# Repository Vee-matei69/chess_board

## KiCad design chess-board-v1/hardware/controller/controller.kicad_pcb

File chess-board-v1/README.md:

Electronic chess board

# get the initial board layout - which squares the pieces are on - 
when initializing, each piece is given a xpos and ypos

# if a piece is lifted, scan the board -
-get the new layout of the board - empty squares and occupied squares[current_matrix] - get the row-col (lifted_square)
-go through each board piece and find the one that has xpos and ypos same as the (lifted_square)
-check for possible moves - (check for possible squares) - feed them into an array
-compare the [possible_squares] and [current_matrix] - 
-if 

possible_squares, available_squares, valid_squares

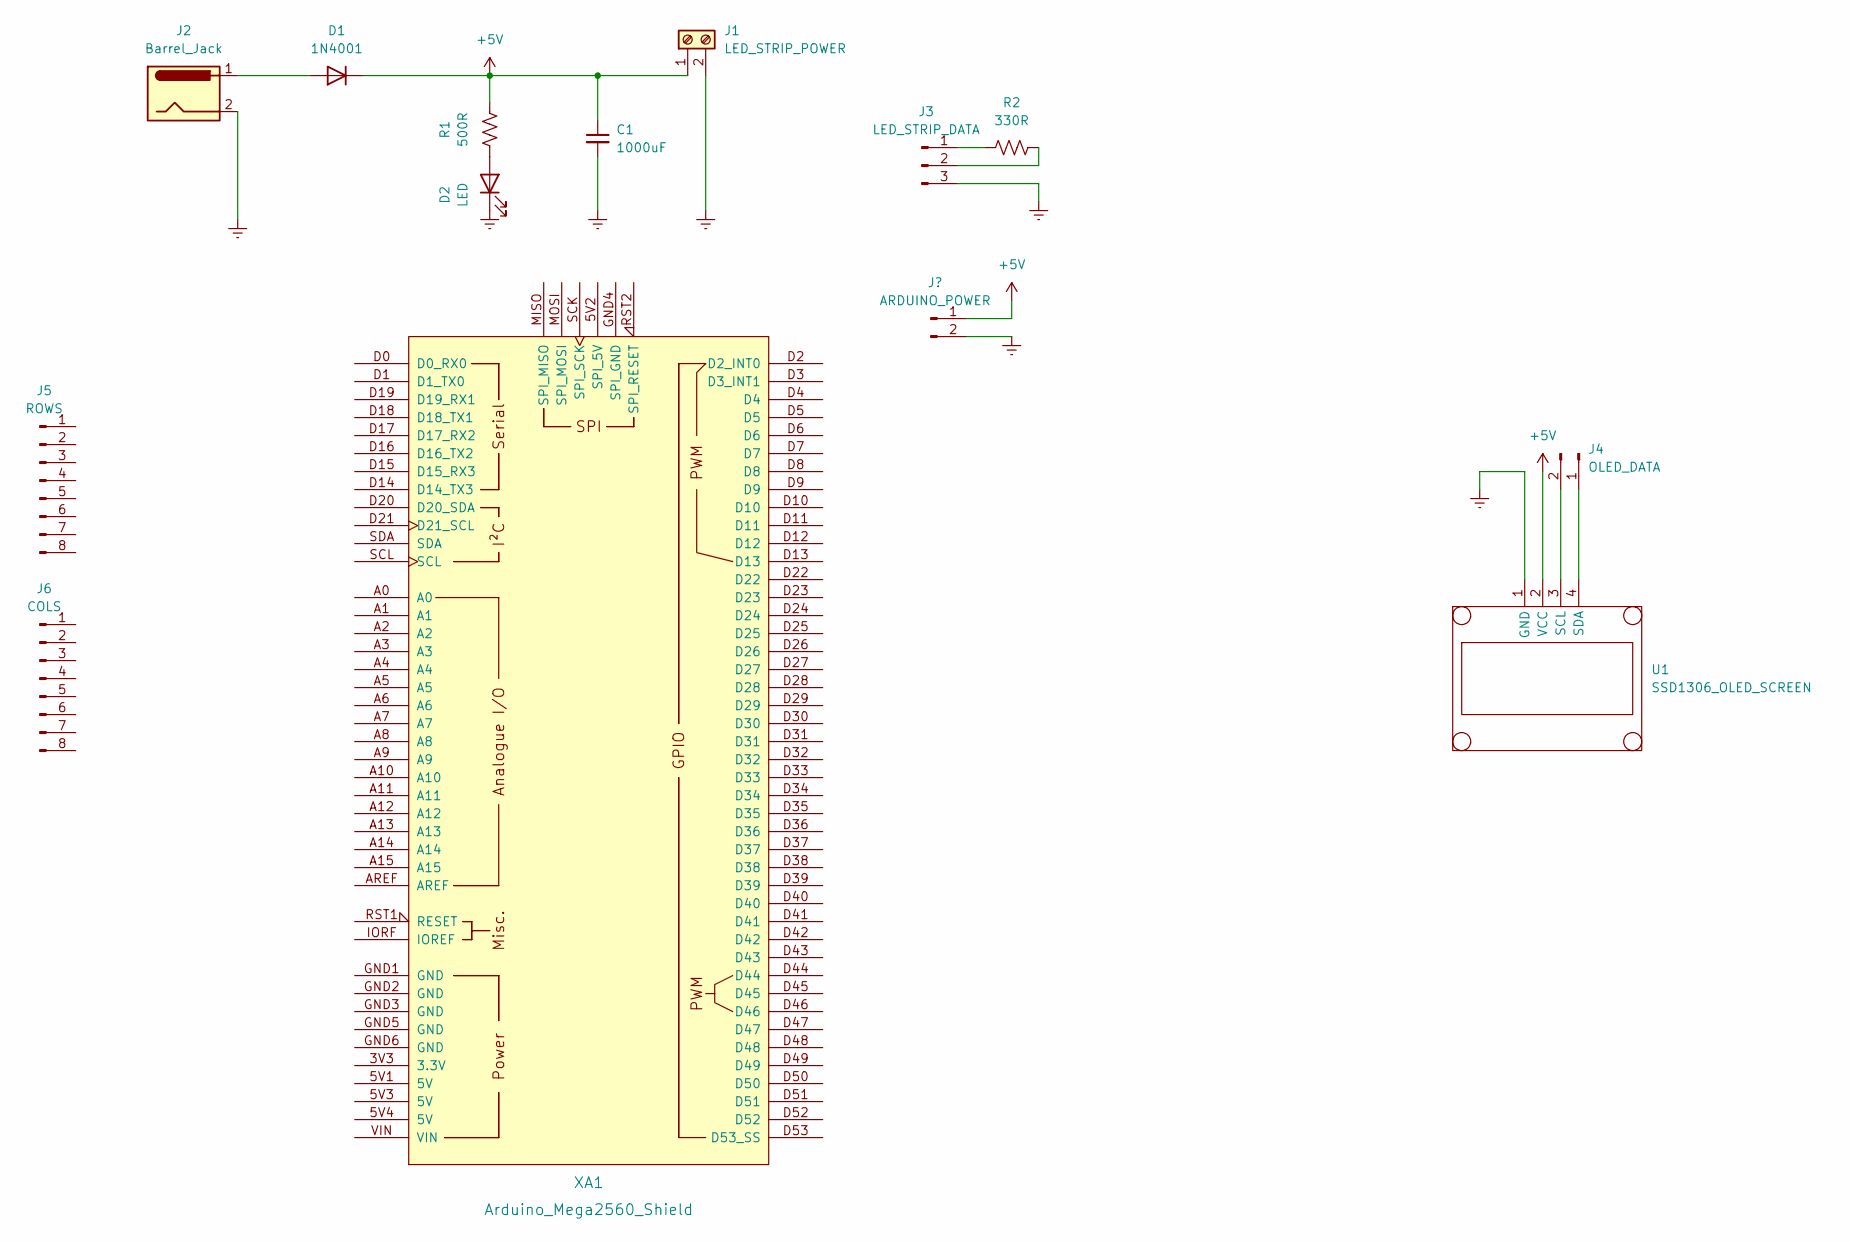
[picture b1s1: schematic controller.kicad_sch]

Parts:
C1: 1000uF; CP_Radial_D8.0mm_P3.50mm
D1: 1N4001; D_DO-41_SOD81_P10.16mm_Horizontal
D2: LED; LED_D4.0mm
J1: LED_STRIP_POWER; TerminalBlock_bornier-2_P5.08mm
J2: Barrel_Jack; BarrelJack_Wuerth_6941xx301002
J3: LED_STRIP_DATA; PinHeader_1x03_P2.54mm_Vertical
J4: OLED_DATA; PinHeader_1x02_P2.54mm_Vertical
J5: ROWS; PinHeader_1x08_P2.54mm_Vertical
J6: COLS; PinHeader_1x08_P2.54mm_Vertical
R1: 500R; R_Axial_DIN0204_L3.6mm_D1.6mm_P7.62mm_Horizontal
R2: 330R; R_Axial_DIN0204_L3.6mm_D1.6mm_P7.62mm_Horizontal
U1: SSD1306_OLED_SCREEN
XA1: Arduino_Mega2560_Shield

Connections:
+5V: C1.1, D1.1 (K), J1.1, R1.2, U1.2 (VCC); also elsewhere on the board
Earth: C1.2, D2.1 (K), J1.2, J2.2, J3.3, U1.1 (GND); also elsewhere on the board
unnamed: D1.2 (A), J2.1
unnamed: D2.2 (A), R1.1
unnamed: J4.1, U1.4 (SDA)
unnamed: J4.2, U1.3 (SCL)
unnamed: J3.1, R2.1
unnamed: J3.2, R2.2

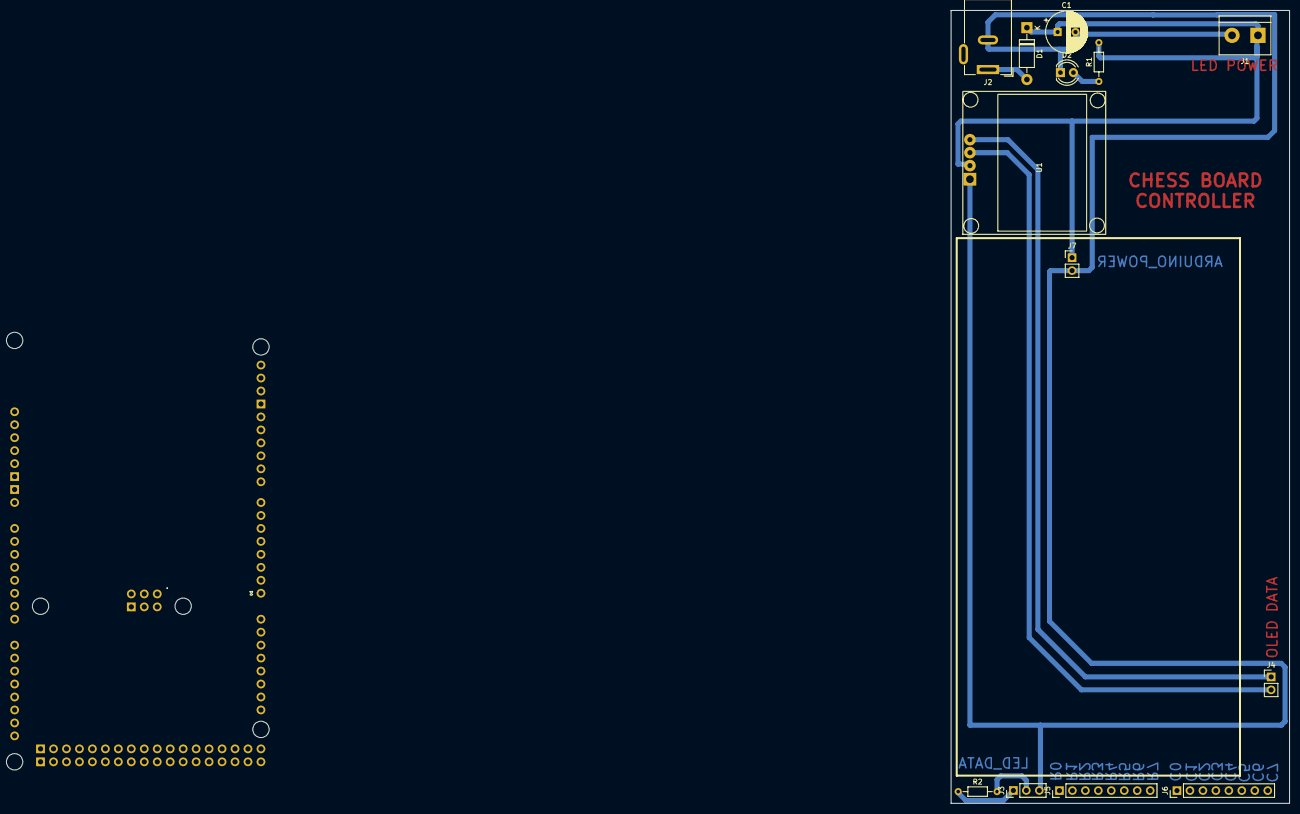
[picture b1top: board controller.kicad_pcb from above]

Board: 2 copper layers, 66.3 x 155.3 mm, 14 parts (0 on the bottom side), 8 nets.

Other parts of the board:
J7: ARDUINO_POWER; PinHeader_1x02_P2.54mm_Vertical

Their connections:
+5V: J7.1; also elsewhere on the board
Earth: J7.2; also elsewhere on the board

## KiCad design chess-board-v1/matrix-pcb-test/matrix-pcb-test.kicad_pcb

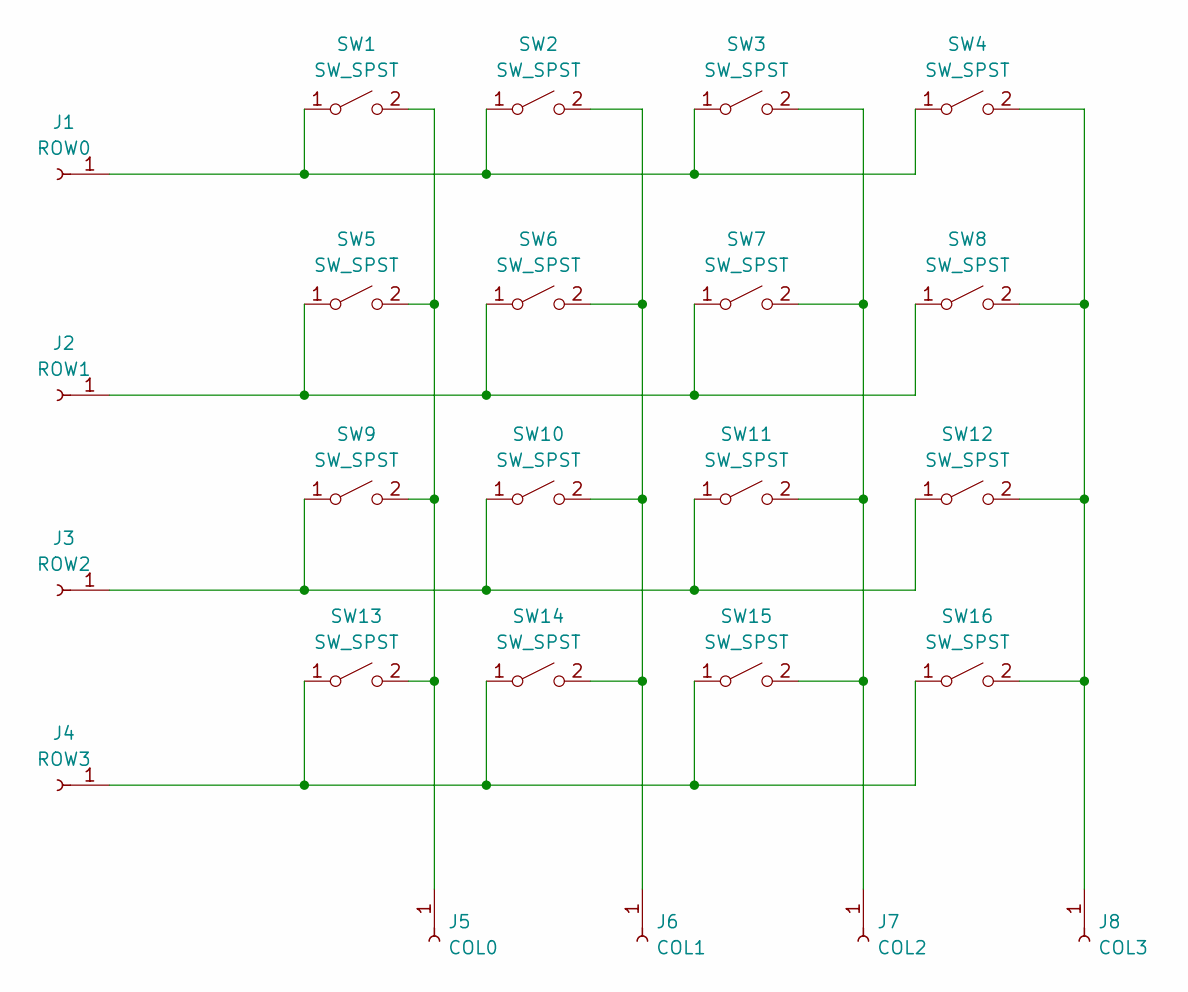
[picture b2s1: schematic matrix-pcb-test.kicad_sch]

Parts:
J1: ROW0; PinSocket_1x01_P2.54mm_Vertical
J2: ROW1; PinSocket_1x01_P2.54mm_Vertical
J3: ROW2; PinSocket_1x01_P2.54mm_Vertical
J4: ROW3; PinSocket_1x01_P2.54mm_Vertical
J5: COL0; PinSocket_1x01_P2.54mm_Vertical
J6: COL1; PinSocket_1x01_P2.54mm_Vertical
J7: COL2; PinSocket_1x01_P2.54mm_Vertical
J8: COL3; PinSocket_1x01_P2.54mm_Vertical
SW1, SW2, SW3, SW4, SW5, SW6, SW7, SW8, SW9, SW10, SW11, SW12, SW13, SW14, SW15, SW16: SW_SPST; matrix-button

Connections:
unnamed: J1.1, SW1.1 (A), SW2.1 (A), SW3.1 (A), SW4.1 (A)
unnamed: J2.1, SW5.1 (A), SW6.1 (A), SW7.1 (A), SW8.1 (A)
unnamed: J3.1, SW9.1 (A), SW10.1 (A), SW11.1 (A), SW12.1 (A)
unnamed: J4.1, SW13.1 (A), SW14.1 (A), SW15.1 (A), SW16.1 (A)
unnamed: J5.1, SW1.2 (B), SW5.2 (B), SW9.2 (B), SW13.2 (B)
unnamed: J6.1, SW2.2 (B), SW6.2 (B), SW10.2 (B), SW14.2 (B)
unnamed: J7.1, SW3.2 (B), SW7.2 (B), SW11.2 (B), SW15.2 (B)
unnamed: J8.1, SW4.2 (B), SW8.2 (B), SW12.2 (B), SW16.2 (B)

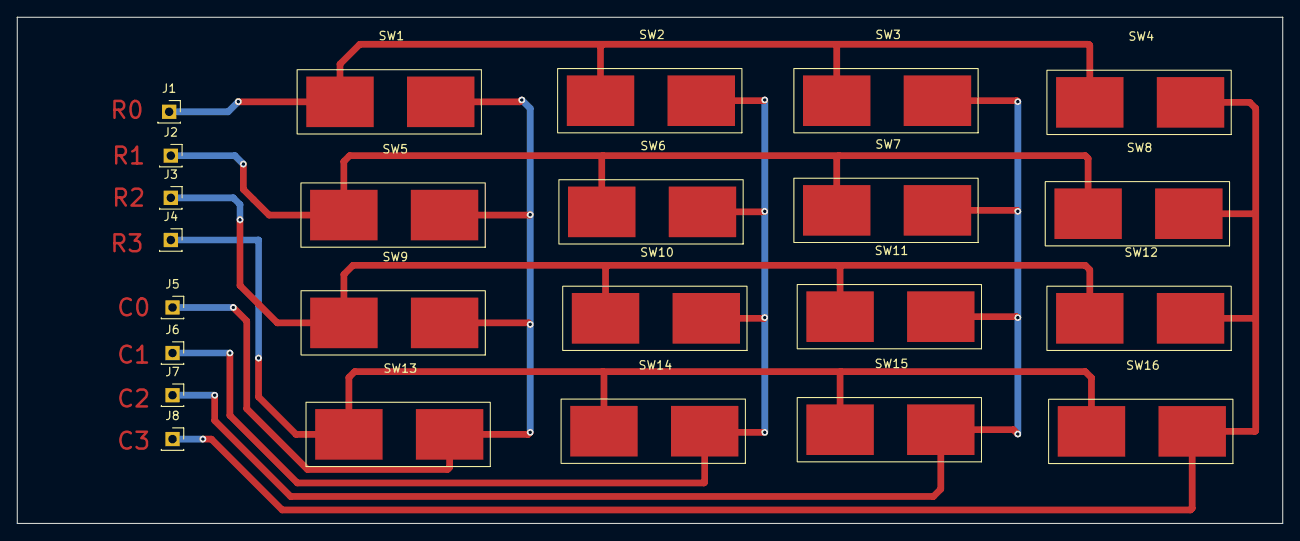
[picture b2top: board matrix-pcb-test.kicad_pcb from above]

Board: 2 copper layers, 150.0 x 60.0 mm, 24 parts (0 on the bottom side), 8 nets.

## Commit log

2023-09-04 added test files
2023-09-05 added main.cpp
2023-09-05 added README.md
2023-09-05 added Piece initialization
2023-09-07 init board
2023-10-20 added board scanner
2023-10-23 added matric scanner code
2023-10-24 added scanning + LEDs
2023-10-29 addedboard initialization
2023-11-01 added chess print
2023-11-09 added piece moves
